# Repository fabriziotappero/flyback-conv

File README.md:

In 2018 Navitas Semiconductor announced what they define the world’s smallest, fastest-charging mobile adapter.
Its schematic is built around a GaNFast power ICs delivering 5x greater power than standard smartphone chargers 
with 2x higher power density.

In the same year, Texas Instruments presented the design of a 70W AC/DC Flyback converter with a power density
of about 30W per cubic inch. Practiacally, this would be a power adapter that is 4 times smaller 
than the 2018 Apple Powerbook wall power adapter.

In this repository you can find an open-source KiCad implementation of a very similar 70W Flyback converter.	

## Electronic Schematic
![][flyback_conv_sch]

[flyback_conv_sch]: https://github.com/fabriziotappero/flyback-conv/blob/master/IMG/flyback_conv_sch.jpeg ""

## Printed Circuit Board
This is the 2 layer PCB designed.

![][flyback_conv_pcb]

[flyback_conv_pcb]: https://github.com/fabriziotappero/flyback-conv/blob/master/IMG/flyback_conv_pcb.jpeg ""

All major developments into high-desity AC/DC flyback converters are done around fancy GaN Mosfets that are 
not so readly available. For instance, the Texas Intruments TIDA-01622 schematic is built around the Navitas 
Semiconductor NV6117 and the NV6115.

At the time of writing (04/2018) the only GaN Mosfet available to me is the Panasonic PGA26E07BA or the cheaper PGA26E19BA.
Both GaN FET would probably require a driver, the Panasonic AN34092B.

The datasheet of all mentioned components are available in the /PDF folder.

## BOM
![][flyback_conv_bom]

[flyback_conv_bom]: https://github.com/fabriziotappero/flyback-conv/blob/master/IMG/flyback_conv_bom.jpeg ""

## References

[KiCad EDA Tool]: (http://kicad-pcb.org/)
[APEC 2017 Active Clamp Flyback Converter]: (https://www.navitassemi.com/wp-content/uploads/2015/03/APEC-2017-Active-Clamp-Flyback-3-29-17.pdf)
[Navitas Semiconductor - White papers]: (https://www.navitassemi.com/white-papers-articles/)

## More Information
For any enquiry contact:

fabrizio.tappero@gmail.com

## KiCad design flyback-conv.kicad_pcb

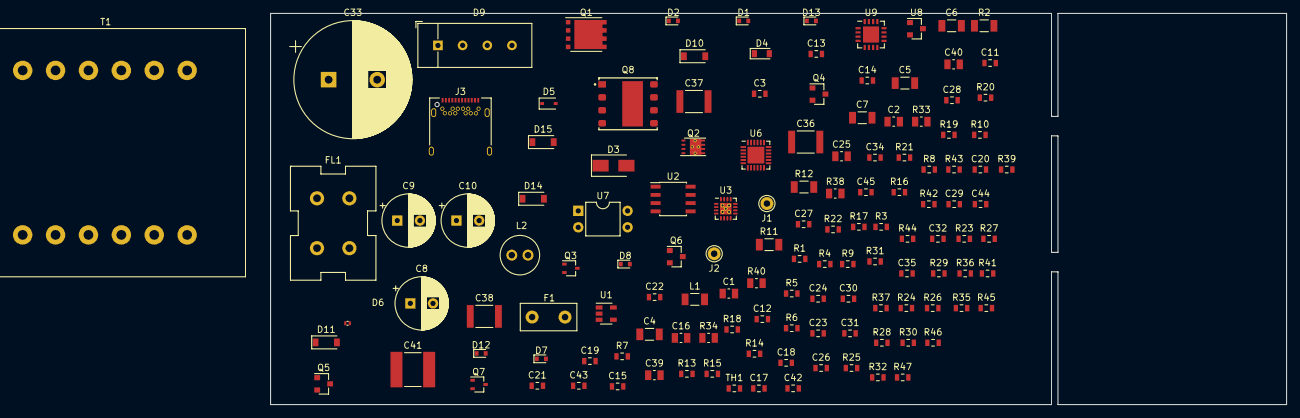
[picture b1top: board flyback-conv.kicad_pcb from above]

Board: 2 copper layers, 156.9 x 60.4 mm, 131 parts (0 on the bottom side), 80 nets, no tracks yet.

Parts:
C1, C2: 2.2uF; C_0805_2012Metric
C3: 220pF/250V; C_0603_1608Metric
C4, C5: 33uF; C_1206_3216Metric
C6, C7: 10uF; C_1206_3216Metric
C8, C9, C10: 270uF; CP_Radial_D8.0mm_P3.50mm
C11, C27, C28, C45: 0.01uF; C_0603_1608Metric
C12: 0.33uF; C_0603_1608Metric
C13, C14, C19, C21, C22: 0.022uF; C_0603_1608Metric
C15: 2200pF; C_0603_1608Metric
C16: 6.8uF; C_0805_2012Metric
C17: 12pF; C_0603_1608Metric
C18: 22pF; C_0603_1608Metric
C20, C44: 3.3pF; C_0603_1608Metric
C23, C24, C26, C30, C32: 0.1uF; C_0603_1608Metric
C25: 4.7uF; C_0805_2012Metric
C29: 1uF; C_0603_1608Metric
C31, C35: 220pF; C_0603_1608Metric
C33: 82uF; CP_Radial_D18.0mm_P7.50mm
C34: 0.22uF; C_0603_1608Metric
C36: 0.47uF; C_1812_4532Metric
C37, C38: 0.22uF/500V; C_1812_4532Metric
C39, C40: 0.47uF; C_0805_2012Metric
C41: 2200pF/250V; C_2220_5650Metric
C42: 560pF; C_0603_1608Metric
C43: 4700pF; C_0603_1608Metric
D1: SDM03U40-7; D_SOD-523
D2: BZT52C22T-7; D_SOD-523
D3: B340A-13-F; D_SMA
D4: RFU02VSM6S; TUMD2SM
D5: CDSOD323-T24S; D_SOD-323
D6: TPD1E05U06QDPYRQ; X1SON2
D7, D8: CZRU52C2; D_SOD-523
D9: KBP06G; VISHAY_2KBP
D10: BAV21W-7-F; D_SOD-123
D11: MMSZ5248B-7-F; D_SOD-123
D12, D13: CZRU52C6V2; D_SOD-523
D14, D15: CSFMT108-HF; D_SOD-123
F1: Fuse; Fuse_Littlefuse_395Series
FL1: 20mH; L_CommonMode_Wuerth_WE-CMB-S
J1, J2: HOLE; Pin_D1.0mm_L10.0mm
J3: USB_C_Receptacle; USB_C_Receptacle_Amphenol_12401548E4-2A
L1: 0.68uH; L_1206_3216Metric
L2: 1uH; WURTH_7447462010
Q1: BSC093N15NS5ATMA; VSONP-8-1EP_5x6_P1.27mm
Q2: CSD17578Q3; VSONP-8-1EP_3.3x3.3_P0.65mm
Q3, Q7: 2N7002KW; SOT-323_SC-70
Q4: DMP510DL; SOT-23
Q5: BSS126H6906; SOT-23
Q6: MMBTA42; SOT-23
Q8: PGA26E07; PANASONIC_PGA26E07BA
R1, R37: 100R; R_0603_1608Metric
R2: 22R; R_1206_3216Metric
R3, R5, R6, R18, R23, R24, R45: 10R; R_0603_1608Metric
R4: 1k; R_0603_1608Metric
R7, R17: 10k; R_0603_1608Metric
R8, R35: 100k; R_0603_1608Metric
R9: 1.6k; R_0603_1608Metric
R10: 24.9R; R_0603_1608Metric
R11: 0.18R; R_1206_3216Metric
R12: 0.005R; R_1206_3216Metric
R13: 121R; R_0603_1608Metric
R14: 2R; R_0603_1608Metric
R15, R32: 1M; R_0603_1608Metric
R16: 69.8k; R_0603_1608Metric
R19: 82.5k; R_0603_1608Metric
R20: 221k; R_0603_1608Metric
R21, R39: 0R; R_0603_1608Metric
R22: 2k; R_0603_1608Metric
R25: 61.9k; R_0603_1608Metric
R26: 90.9k; R_0603_1608Metric
R27: 191k; R_0603_1608Metric
R28: 56.2k; R_0603_1608Metric
R29: 47.5k; R_0603_1608Metric
R30: 27k; R_0603_1608Metric
R31: 22.1k; R_0603_1608Metric
R33, R34: 1M; R_0805_2012Metric
R36: 75k; R_0603_1608Metric
R38, R40: 1R; R_0805_2012Metric
R41: 11k; R_0603_1608Metric
R42: 562R; R_0603_1608Metric
R43: 34k; R_0603_1608Metric
R44: 60.4k; R_0603_1608Metric
R46, R47: 150k; R_0603_1608Metric
T1: 150-2670; Transformer_37x44
TH1: 47k; R_0603_1608Metric
U1: UCC24612; SOT-23-5
U2: ISO7710; SOIC-8_3.9x4.9mm_P1.27mm
U3: UCC28780; QFN-16-1EP_3x3mm_P0.5mm_EP2.7x2.7mm_ThermalVias
U6: TPS25740B; QFN-24-1EP_4x4mm_P0.5mm_EP2.6x2.6mm
U7: SFH617A-1; DIP-4_W7.62mm
U8: ATL431; SOT-23
U9: AN34092B; QFN-16-1EP_4x4mm_P0.65mm_EP2.5x2.5mm

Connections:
/CC2: C42.1, D6.1, J3.B5, U6.3
/CS: C17.1, R9.2, U3.1
/DVDD: C34.1, U6.5, U6.13
/F: Q1.3, R1.1, R2.2
/FB: C31.2, R31.2, R32.1, U3.10
/GDNG: R3.2, R4.1, U6.22
/GDNS: Q2.1, R10.2, R12.2, U6.23
/INH: R18.2, U2.6
/ISNS: C12.2, R10.1, U6.19
/L: F1.2, J1.1
/N: FL1.4, J2.1
/PWMH: R6.2, U3.3
/RUN: D1.2, Q3.1, Q7.1, R8.2, U3.4
/S: C4.1, C5.1, L1.1, L2.1
/VBUS: C12.1, C16.1, D3.1, J3.A4, J3.A9, J3.B4, J3.B9, R12.1, R37.1, U6.21
/VCC1: C14.1, D8.2, U2.1, U2.3
/VCC2: C19.1, D7.2
/VCCH: C21.1, D4.1, R29.2
/VCCL: C13.1, C22.1, Q4.3, R14.2
/VDD: C23.1, C25.1, C29.1, D10.1, R5.2, R38.2, U3.15
/VS: D14.2, R16.1, T1.3
/VSW: C19.2, C20.2, C21.2, C27.2, D12.2, Q5.3, T1.2, U2.5, U2.7
/Vaux: C32.1, U6.14, U6.15, U6.16
/Vo: C1.1, C6.1, C7.1, C8.1, C9.1, C10.1, C26.1, L1.2, L2.2, Q2.3, R45.1, U1.4, U6.20
/Vref: C24.2, C31.1, R27.1, U3.14
CTL: C44.1, C45.1, R21.2, R22.2, R39.1, R46.2, R47.1, U8.2
Earth: C15.2, C17.2, C18.2, C23.2, C24.1, C25.2, C29.2, C33.2, C35.1, C36.2, C39.1, C40.1, C41.2, D2.2, D5.2, D9.4, D11.2, Q7.2, R11.2, R17.2, R19.1, R20.1, R28.2, T1.4, TH1.1, U3.8, U3.16, U3.17, U7.3
GND: C1.2, C2.2, C3.1, C4.2, C5.2, C6.2, C7.2, C8.2, C9.2, C10.2, C11.2, C16.2, C26.2, C30.2, C32.2, C34.2, C41.1, C42.2, D3.2, D6.2, J3.A1, J3.A12, J3.B1, J3.B12, J3.S1, Q1.1, R35.1, R47.2, U1.2, U6.4, U6.11, U6.17, U6.18, U6.25, U8.3
unnamed: C2.1, U1.3
unnamed: C3.2, R2.1
unnamed: C11.1, R4.2
unnamed: C13.2, C14.2, C22.2, C28.2, D13.2, R9.1, R11.1, U2.4
unnamed: C15.1, D2.1, Q5.1, R15.1, U3.6
unnamed: C18.1, D5.1, R13.2, R15.2, U3.5
unnamed: C20.1, R18.1
unnamed: C27.1, D7.1, R23.2
unnamed: C28.1, D8.1, R24.2
unnamed: C30.1, U6.1
unnamed: C33.1, C36.1, C37.1, C38.1, D9.1, R33.1, T1.1
unnamed: C35.2, R27.2, R28.1, U3.13
unnamed: C37.2, C38.2, R34.2
unnamed: C39.2, C40.2, Q6.3, R30.1, R40.2
unnamed: C43.1, R42.2
unnamed: C43.2, R41.2, R43.1, U7.1
unnamed: C44.2, R43.2, R44.2, U7.2, U8.1
unnamed: C45.2, R44.1
unnamed: D1.1, D13.1
unnamed: D4.2, R14.1
unnamed: D9.2, FL1.2
unnamed: D9.3, FL1.3
unnamed: D10.2, Q6.2
unnamed: D11.1, Q6.1, R30.2
unnamed: D12.1, R29.1
unnamed: D14.1, R38.1
unnamed: D15.1, R40.1
unnamed: F1.1, FL1.1
unnamed: Q1.2, U1.1
unnamed: Q2.2, R3.1
unnamed: Q3.2, R8.1
unnamed: Q3.3, Q4.1, R7.2
unnamed: Q4.2, R5.1, R7.1
unnamed: Q5.2, R13.1
unnamed: Q7.3, R32.2
unnamed: R1.2, U1.5
unnamed: R6.1, U2.2
unnamed: R16.2, R17.1, U3.7
unnamed: R19.2, U3.12
unnamed: R20.2, U3.11
unnamed: R21.1, R25.2
unnamed: R22.1, R26.2
unnamed: R25.1, U6.6
unnamed: R26.1, U6.7
unnamed: R31.1, U7.4
unnamed: R33.2, R34.1
unnamed: R35.2, U6.12
unnamed: R36.1, R39.2
unnamed: R36.2, U6.8
unnamed: R37.2, U6.24
unnamed: R41.1, R42.1, R45.2, R46.1
unnamed: TH1.2, U3.9

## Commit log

2018-04-19 minor
2018-04-19 fixes some file naming
2018-04-20 added Panasonic GaN mosfet datasheets
2018-05-23 added PDF of many components and completed main schematic
2018-05-23 fixed few lib componentes and screated PCB
2018-05-24 generated BOM v1.0, added some screenshots and added an alternative for the transformer
2018-05-24 minor README error fix
2018-05-24 minor modif
